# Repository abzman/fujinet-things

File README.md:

# fujinet-things
progress getting fujinet onto various platforms

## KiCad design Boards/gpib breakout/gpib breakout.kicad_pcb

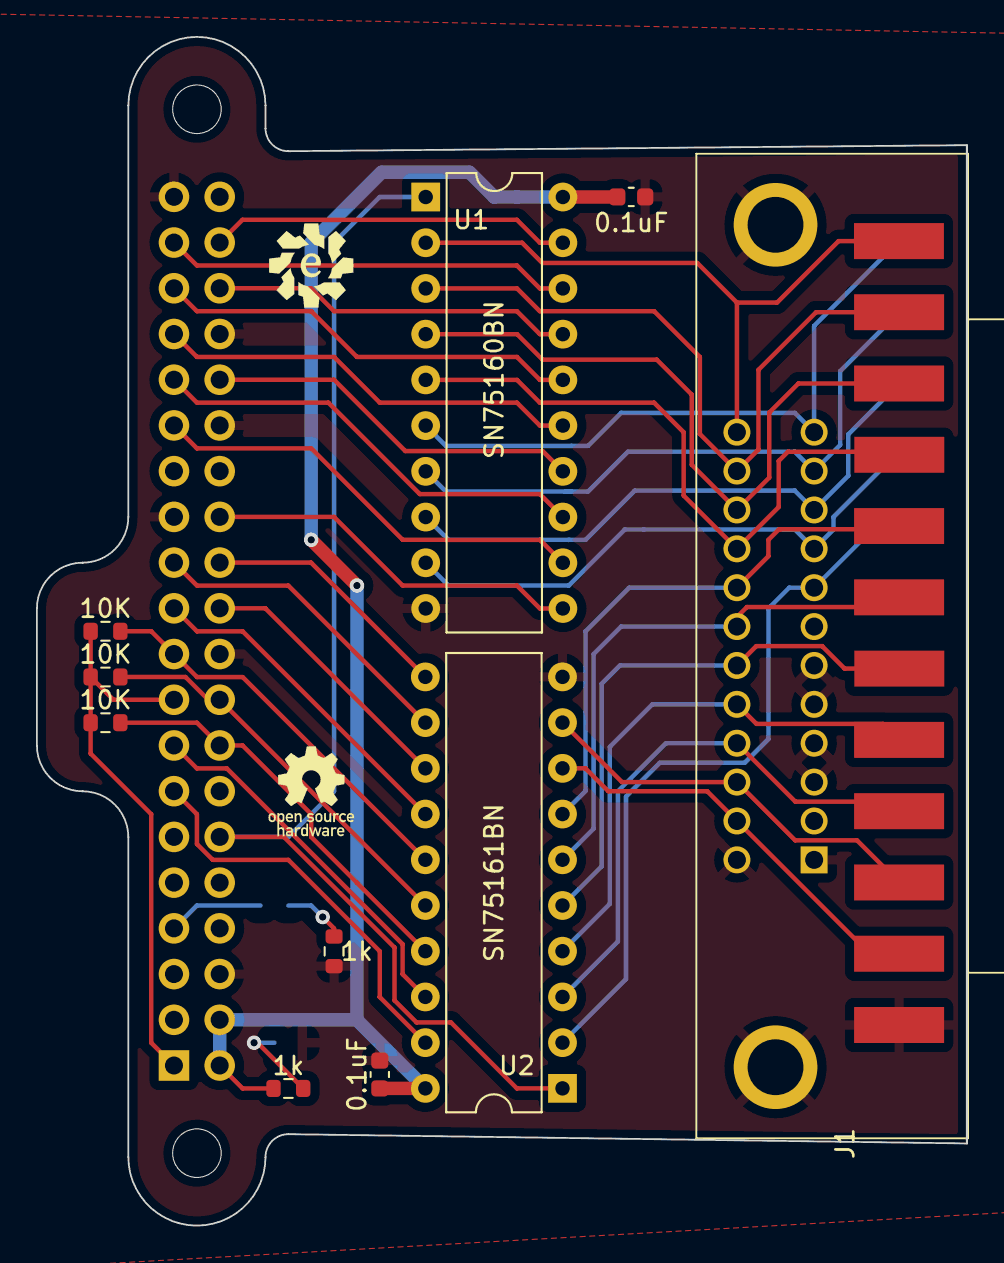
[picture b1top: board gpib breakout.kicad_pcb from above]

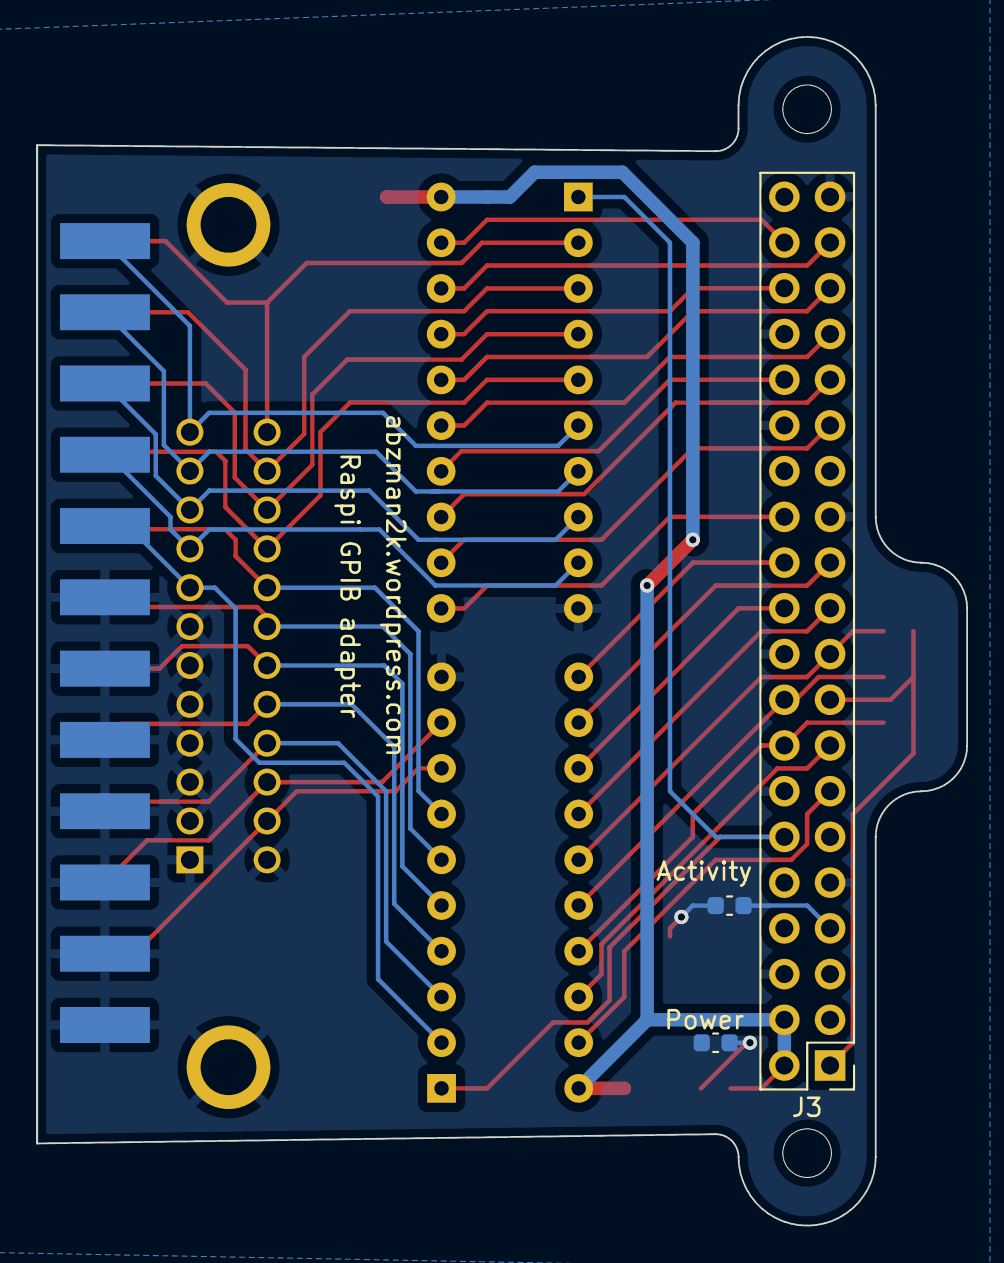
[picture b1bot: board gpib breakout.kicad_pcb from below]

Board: 2 copper layers, 51.7 x 66.0 mm, 14 parts (3 on the bottom side), 41 nets.

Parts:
C1, C2: 0.1uF; C_0603_1608Metric
D1: Activity; C_0603_1608Metric
D2: Power; C_0603_1608Metric
J1: 2x12 card edge connector (lettered/numbered); edge mounted 24 pin card edge connector (2x12 pin)
J2: 112-024-113R001; GPIB
J3: Raspberry_Pi_2_3; PinHeader_2x20_P2.54mm_Vertical
R1, R2, R3: 10K; R_0603_1608Metric
R4, R5: 1k; R_0603_1608Metric
U1: SN75160BN; DIP-20_W7.62mm
U2: SN75161BN; DIP-20_W7.62mm

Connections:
+3V3: J3.1 (3V3), J3.17 (3V3), R1.1, R2.1, R3.1
+5V: C1.1, C2.1, J3.2 (5V), J3.4 (5V), R5.2, U1.20 (VCC), U2.20 (VCC)
/ATN: J1.11, J2.11, U2.8 (ATN_1)
/DAV: J1.6, J2.6, U2.6 (DAV_1)
/DIO1: J1.1, J2.1, U1.2 (B1)
/DIO2: J1.2, J2.2, U1.3 (B2)
/DIO3: J1.3, J2.3, U1.4 (B3)
/DIO4: J1.4, J2.4, U1.5 (B4)
/DIO5: J1.A, J2.13, U1.6 (B5)
/DIO6: J1.B, J2.14, U1.7 (B6)
/DIO7: J1.C, J2.15, U1.8 (B7)
/DIO8: J1.D, J2.16, U1.9 (B8)
/EOI: J1.5, J2.5, U2.7 (EOI_1)
/GPIO05: J3.29 (GCLK1/GPIO5), U1.12 (D8)
/GPIO06: J3.31 (GCLK2/GPIO6), U1.13 (D7)
/GPIO07: J3.26 (~CE1/GPIO7), U1.11 (~PE)
/GPIO08: J3.24 (~CE0/GPIO8), U2.11 (DC)
/GPIO09: J3.21 (MISO0/GPIO9), U2.14 (EOI_2)
/GPIO10: J3.19 (MOSI0/GPIO10), R3.2, U2.15 (DAV_2)
/GPIO11: J3.23 (SCLK0/GPIO11), U2.12 (SRQ_2)
/GPIO12: J3.32 (PWM0/GPIO12), U1.14 (D6)
/GPIO13: J3.33 (PWM1/GPIO13), U1.15 (D5)
/GPIO16: J3.36 (GPIO16), U1.17 (D3)
/GPIO18: J3.12 (GPIO18/PWM0), U1.1 (TE), U2.1 (TE)
/GPIO19: J3.35 (GPIO19/MISO1), U1.16 (D4)
/GPIO20: J3.38 (GPIO20/MOSI1), U1.19 (D1)
/GPIO22: J3.15 (GPIO22), U2.18 (IFC_2)
/GPIO23: J3.16 (GPIO23), R1.2, U2.17 (NDAC_2)
/GPIO24: J3.18 (GPIO24), R2.2, U2.16 (NRFD_2)
/GPIO25: J3.22 (GPIO25), U2.13 (ATN_2)
/GPIO26: J3.37 (GPIO26), U1.18 (D2)
/GPIO27: J3.13 (GPIO27), U2.19 (REN_2)
/IFC: J1.9, J2.9, U2.3 (IFC_1)
/NDAC: J1.8, J2.8, U2.4 (NDAC_1)
/NRFD: J1.7, J2.7, U2.5 (NRFD_1)
/REN: J1.E, J2.17, U2.2 (REN_1)
/SRQ: J1.10, J2.10, U2.9 (SRQ_1)
GND: C1.2, C2.2, D2.1 (K), J1.12, J1.F, J1.H, J1.J, J1.K, J1.L, J1.M, J1.N, J2.12, J2.18, J2.19, J2.20, J2.21, J2.22, J2.23, J2.24, J2.MH1, J2.MH2, J3.6 (GND), J3.9 (GND), J3.14 (GND), J3.20 (GND), J3.25 (GND), J3.30 (GND), J3.34 (GND), J3.39 (GND), R4.2, U1.10 (GND), U2.10 (GND)
unnamed: D1.1 (K), R4.1
unnamed: D1.2 (A), J3.7 (GCLK0/GPIO4)
unnamed: D2.2 (A), R5.1

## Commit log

2022-01-25 first commit (esp32 and gpib breakouts)
2022-03-02 moved LEDs to the other side of the board
2022-05-09 started trs80 model 100 latout
2022-05-09 tweaked bus interface for 8085
2022-05-13 working on s100 stuff
2022-05-18 updated s100 spi board
2022-11-25 added gitignore
2023-11-03 moved gpib breakout to small useful pcbs
    https://github.com/abzman/small-useful-PCBs
2023-11-03 moved esp breakout to other repo
    https://github.com/abzman/esp-IoT-boards
